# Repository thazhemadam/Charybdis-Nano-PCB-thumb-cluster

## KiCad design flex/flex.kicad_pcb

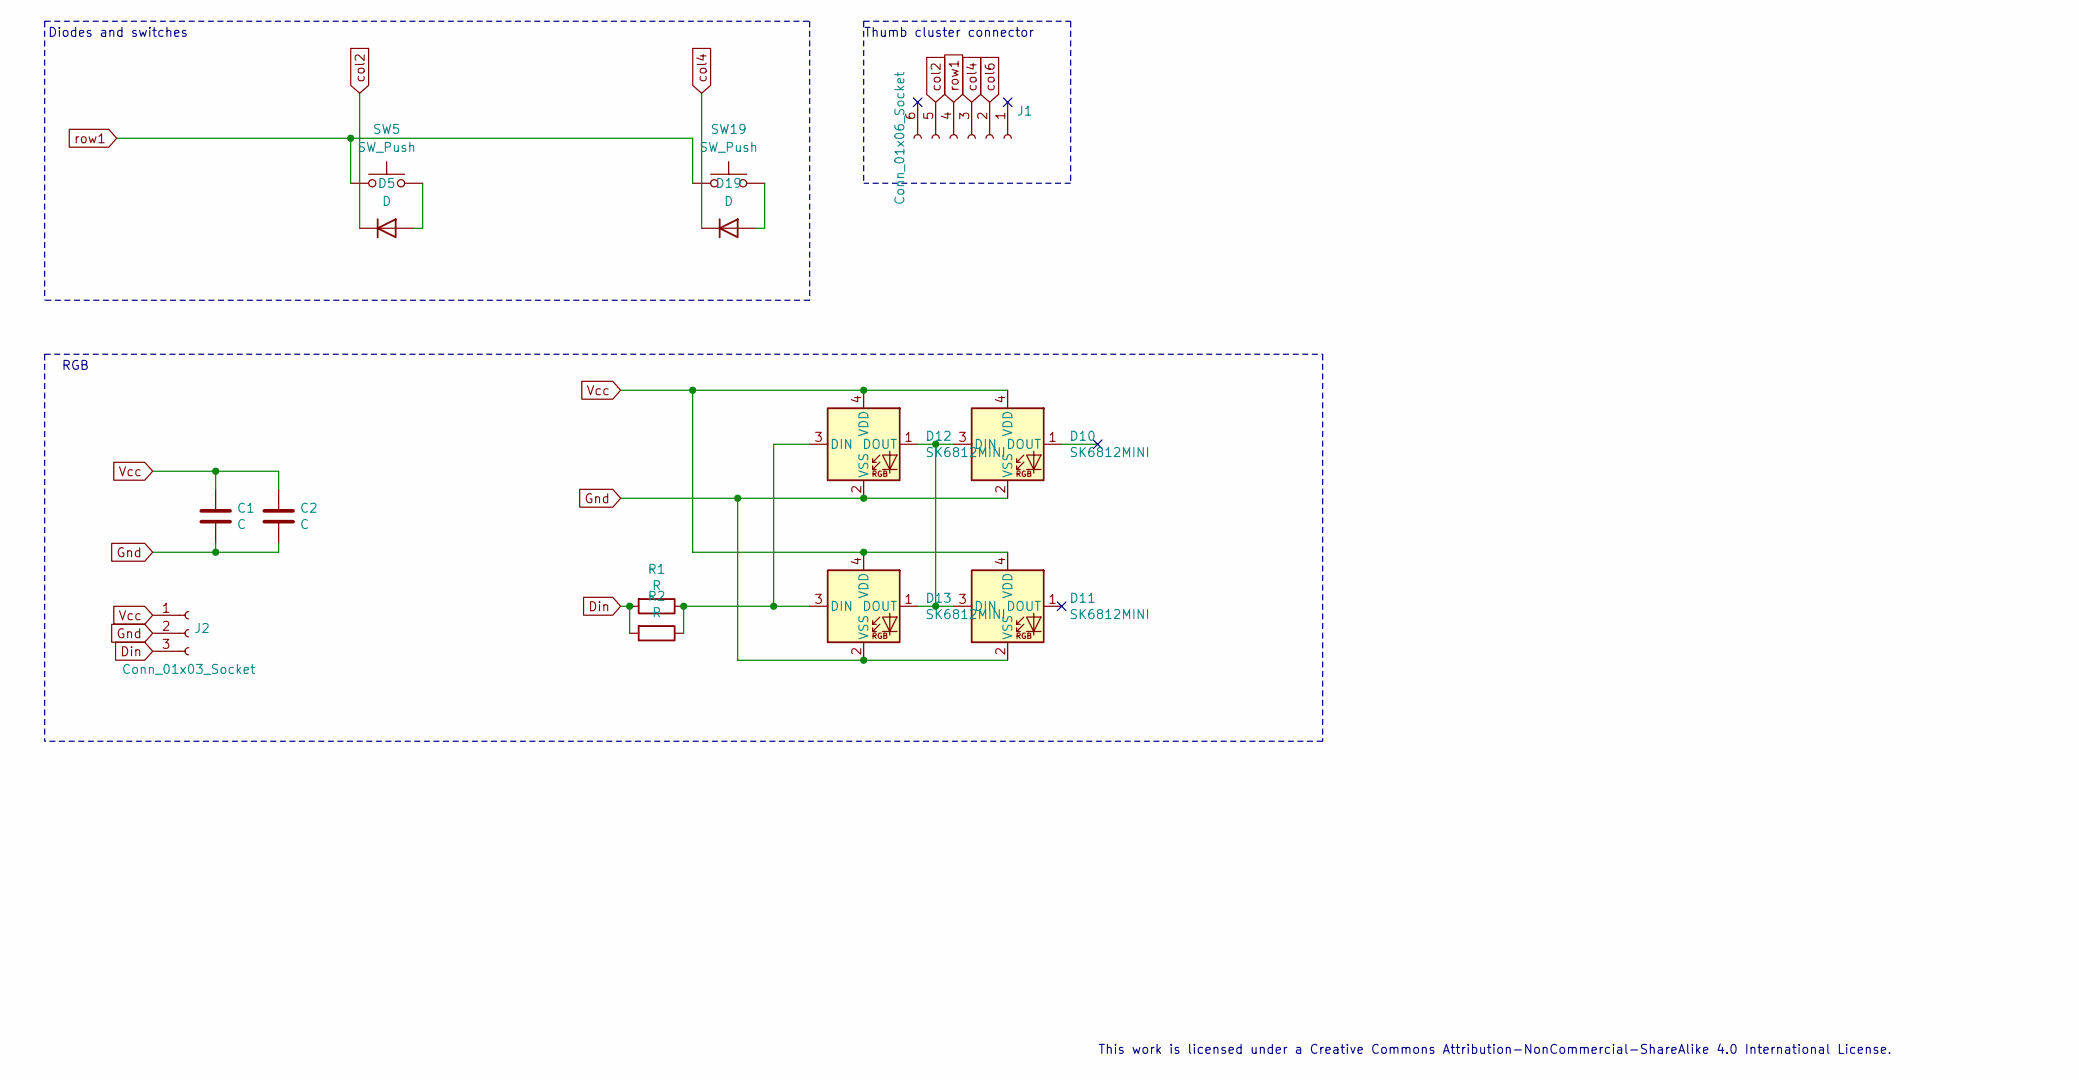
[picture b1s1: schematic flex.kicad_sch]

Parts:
C1, C2: C; LED_1206_3216Metric_Pad1.42x1.75mm_HandSolder
D5, D19: D; Diode_TH_SOD123
D10, D11, D12, D13: SK6812MINI; LED_SK6812MINI_PLCC4_3.5x3.5mm_P1.75mm
J1: Conn_01x06_Socket
J2: Conn_01x03_Socket
R1, R2: R; R_1206_3216Metric_Pad1.42x1.75mm_HandSolder
SW5, SW19: SW_Push; SW_MX_reversible

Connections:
Din: J2.3, R1.2, R2.2
Gnd: C1.2, C2.2, D10.2 (VSS), D11.2 (VSS), D12.2 (VSS), D13.2 (VSS), J2.2
unnamed: D5.2 (A), SW5.2
unnamed: D10.1 (DOUT), D11.1 (DOUT)
unnamed: D10.3 (DIN), D11.3 (DIN), D12.1 (DOUT), D13.1 (DOUT)
unnamed: D12.3 (DIN), D13.3 (DIN), R1.1, R2.1
unnamed: D19.2 (A), SW19.2
Vcc: C1.1, C2.1, D10.4 (VDD), D11.4 (VDD), D12.4 (VDD), D13.4 (VDD), J2.1
col2: D5.1 (K), J1.5
col4: D19.1 (K), J1.3
col6: J1.2
row1: J1.4, SW5.1, SW19.1

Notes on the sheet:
Thumb cluster connector
Diodes and switches
RGB
This work is licensed under a Creative Commons Attribution-NonCommercial-ShareAlike 4.0 International License.

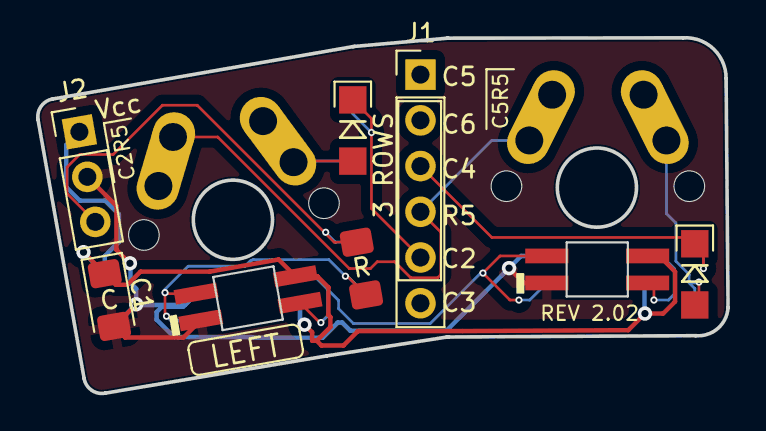
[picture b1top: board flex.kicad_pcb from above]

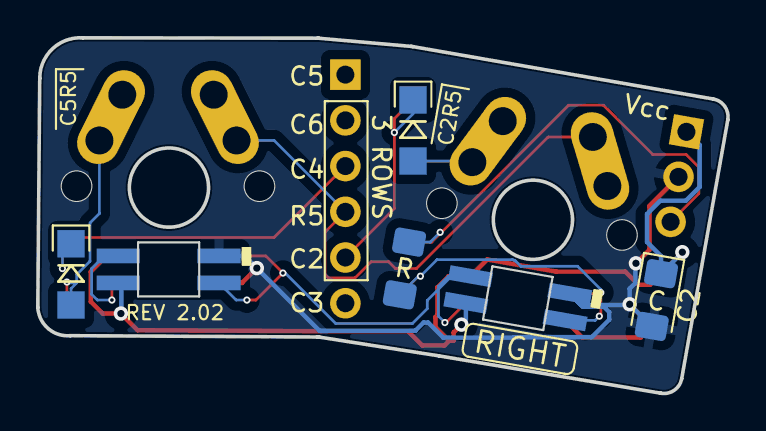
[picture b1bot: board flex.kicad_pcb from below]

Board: 2 copper layers, 38.3 x 19.8 mm, 14 parts (4 on the bottom side), 11 nets.

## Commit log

2024-06-11 update to kicad 8
2024-06-11 update gitignore
2024-06-11 pcb: remove breakout tabs and extra stuff
2024-06-11 sch: update symbols from library and fix erc
2024-06-11 remove breakaway thumb

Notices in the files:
flex/flex.kicad_sch:
CC BY-NC-SA 4.0
Copyright Quentin Lebastard 2022
